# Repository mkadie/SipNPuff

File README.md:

# Sip and Puff Rubber Chicken Edition

## Project Overview

This project implements a functional sip and puff switch interface that serves as both a demonstration system (using rubber chickens) and a working, low-cost ($25-50) sip and puff device for accessibility applications. The core functionality focuses on creating a reliable, accessible interface while using the rubber chicken concept as an engaging demonstration tool for normally abled users.

---

## ⭐ Primary Claim to Fame: One Build, Many Purposes — Text File Configuration

> **The defining characteristic of this project is flexibility.**

Most open-source sip and puff devices are purpose-built for a single output: a USB mouse, a keyboard emulator, or a specific AT protocol. Changing what the device *does* means reflashing firmware or editing code. This project takes a different approach: **a single hardware build and a single firmware image that can be reconfigured for completely different tasks by editing a plain text configuration file** — no compiler, no IDE, no programmer required.

A clinician, caregiver, or technically capable user can open the config file (accessible as a USB drive when the device is plugged in) and change:
- What a sip or puff event maps to (keypress, mouse button, joystick axis, HID consumer control, serial command, etc.)
- Sensitivity thresholds for sip and puff, independently
- Operating mode (USB HID mouse, USB HID keyboard, XAC gamepad output, serial AT command relay, etc.)
- Head-tracking parameters (dead zone, speed curve, re-centre trigger gesture)
- Display content and feedback behaviour

The same physical device can serve as:
- A USB mouse (head tracking + sip/puff clicks)
- A two-switch keyboard input (sip = one key, puff = another)
- An Xbox Adaptive Controller input (via the onboard TRRS jacks)
- A demonstration interface (rubber chicken mode for Maker faires)
- A research data collection tool (with optional microSD logging)

No other project in the open-source sip and puff space offers this level of reconfigurability without touching firmware. This is intentional and is the core design goal that drives decisions about display hardware, the EXTERNAL_IO connector, STEMMA QT expansion, and the overall software architecture.

---

## Project Stage

Early, rapid development for prototype by Maker event, which one ... hopefully the next one :)

> **Firmware reference:** see [`FIRMWARE_NOTES.md`](./FIRMWARE_NOTES.md)
> for the current state of the CircuitPython firmware — pressure-sensor
> fusion, event-classifier rules, the on-screen HUD layout, the repeat-rate
> map, IMU pointing, and the full config-key reference. That's the document
> to read before touching `source/breath_classifier.py`,
> `source/sip_puff_device.py`, or any `config.txt` on a deployed device.

## Core Mission

### Primary Focus: Flexibility Through Text File Configuration
The defining goal is a single hardware and software build that can be reconfigured for a wide range of tasks by editing a plain text config file — no reflashing, no coding skills required. The same device adapts to the user, rather than requiring the user to adapt to a fixed device behavior.

### Secondary Focus: Functional Accessibility Interface
The main objective is to develop a robust, affordable sip and puff switch system that can be used for:
- Assistive technology for individuals with motor disabilities
- Accessibility solutions for communication devices
- Research in human-computer interaction
- Educational demonstrations in accessibility technology

### Tertiary Focus: Demonstration and Engagement
The rubber chicken concept serves as an engaging demonstration tool for:
- Maker faires and community events
- Educational outreach programs
- Public demonstrations of accessibility technology
- Engaging users in the concept of assistive interfaces

## Hardware Design

### Primary Components

#### Sensors

> **PCB Strategy:** Initial PCBs support both sensor footprints simultaneously. After real-world testing, separate PCB variants (SMD-only and through-hole) will be produced.

##### Default Sensor: LPS28DFWTR (SMD — I²C digital)
- **Part:** STMicroelectronics LPS28DFWTR
- **Package:** CCLGA-7L, 2.8 × 2.8 × 1.95 mm — SMD only, requires reflow or hot-air soldering
- **Why it's default:** Water-resistant package (potting gel, rated 10 ATM), 24-bit resolution, ultra-low noise (0.32 Pa), factory-calibrated, I²C interface, embedded FIFO, interrupt output, and 1.7 µA idle current
- **Interface:** I²C (up to 400 kHz fast mode; 1 MHz fast mode+) — connects directly to Pico W I²C bus
- **I²C address:** 0x5C (SA0 pin → GND) or 0x5D (SA0 pin → VDD) — selectable via PCB solder bridge
- **Pressure range:** Mode 1: 260–1260 hPa (optimised for sip/puff); Mode 2: 260–4060 hPa
- **Pressure noise:** 0.32 Pa RMS (Mode 1) — more than sufficient for breath detection
- **Accuracy:** ±0.5 hPa absolute, ±0.015 hPa relative
- **ODR:** 1–200 Hz (software configurable)
- **Supply voltage:** 1.7 to 3.6 V (3.3V from Pico W is within spec)
- **Interrupt:** INT_DRDY pin — data-ready interrupt for efficient polling
- **Datasheet:** DS13317 Rev 1, December 2021 (ST Microelectronics)
- **Sensor Placement:** Positioned in breath path between mouthpiece filter and PCB; water-resistant package tolerates condensation exposure

##### Alternative Sensor: MPX5010DP (Through-Hole — Analog output)
- **Part:** NXP/Freescale MPX5010DP
- **Package:** Through-hole SIP-6 — can be hand-soldered without SMD equipment
- **Why it's an alternative:** Easier to hand-solder for early prototypes and events; no SMD tools required
- **Interface:** **Analog voltage output** (0.2V–4.7V at 5V supply) — connects to a Pico ADC pin, **NOT I²C**
- **Pressure range:** 0–10 kPa differential
- **Supply voltage:** 2.7–5.5V (note: at 3.3V supply the output range scales; verify output headroom in firmware)
- **Accuracy:** ±1.5% FS
- **Power consumption:** ~6 mA typical (significantly higher than LPS28DFWTR)
- **Sensor Placement:** Same breath-path position; analog output wire routes to GPIO 26 (ADC0) on Pico W

#### Microcontroller
- **Raspberry Pi RP2040**: Chosen for its cost-effectiveness ($4), dual-core ARM Cortex-M0+ processor, and sufficient processing power for signal conditioning
- **Alternative Options**: 
  - ESP32 for WiFi connectivity
  - Arduino Nano for simpler implementations
  - STM32 for higher performance applications
- **Processing Requirements**: Signal filtering, input classification, and output protocol handling

#### Mechanical Interface
- **Primary Sip/Puff Mechanism**: 
  - Standard straw or tube for suction input
  - Blow tube for pressure input
  - Ergonomic design for comfortable use
- **Alternative Interfaces**: 
  - Custom 3D printed mouthpieces
  - Commercial sip/puff devices
  - Modular interface system for different user needs
- **Enclosure Design**: 
  - Durable, medical-grade materials
  - Easy-to-clean surfaces
  - Ergonomic housing for various user groups
- **Interface Options**: 
  - Standard straw configuration
  - Bellows system for precise suction detection
  - Custom mouthpiece designs

#### Optional Display Connectors

> Both connectors are unpopulated PCB footprints — built-in hardware support with no board redesign needed to add displays later.

##### J1 — I²C OLED Display (1", 128×64)
- **Connector**: 4-pin 2.54 mm Dupont header on PCB
- **Display type**: 1" 128×64 OLED, SSD1306 controller (or compatible)
- **Interface**: I²C — shares existing GPIO 4 (SDA) / GPIO 5 (SCL) bus with the LPS28DFWTR sensor
- **I²C address**: 0x3C (default) or 0x3D — no conflict with LPS28DFWTR at 0x5C/0x5D
- **Supply**: 3.3V
- **Pin order (1→4)**: GND → VCC → SCL → SDA
- **Use case**: Status readout, sip/puff feedback, pressure level bar graph

##### J2 — SPI Color LCD Display (2"–4")
- **Connector**: 9-pin 2.54 mm Dupont header on PCB
- **Display type**: 2"–4" color TFT LCD, ST7789 or ILI9341 controller (or compatible)
- **Interface**: SPI1 hardware peripheral on dedicated non-analog GPIO pins
- **GPIO assignments**:
  - GPIO 10 — SCK (SPI1 clock)
  - GPIO 11 — MOSI / SDI (SPI1 TX)
  - GPIO 12 — MISO / SDO (SPI1 RX, optional)
  - GPIO 13 — CS (chip select, active low)
  - GPIO 14 — DC/RS (high = data, low = command)
  - GPIO 15 — RESET (active low)
  - GPIO 16 — LED (backlight PWM; solder bridge for always-on 3.3V)
- **Pin order (1→9)**: VCC → GND → CS → RESET → DC/RS → MOSI → SCK → LED → MISO
- **Supply**: 3.3V
- **Use case**: Full-color rubber chicken game interface, animated demo display

#### Circuit Protection

> **A commonly overlooked step in open-source hardware projects, including many assistive technology designs.** External-facing I/O lines that connect to the real world — connectors, encoder inputs, expansion ports — are exposed to ESD events and electrical transients. Protecting the microcontroller's GPIO pins from these events is straightforward and inexpensive; skipping it is a common cause of latent damage in both hobby and clinical builds.

- **IC:** SP724AHTG — low-capacitance TVS (transient voltage suppressor) diode array, STMicroelectronics
- **Coverage:** All external-facing I/O lines **not** already protected by opto-isolation:
  - EXTERNAL_IO connector: BUTTON (GPIO 20), ROT_A (GPIO 18), ROT_B (GPIO 19), SDA (GPIO 4), SCL (GPIO 5)
  - STEMMA QT expansion port (SDA, SCL)
  - Display connectors J1 and J2 signal lines as applicable
- **Not needed on:** GPIO 0 (SIP_ENABLE) and GPIO 1 (PUF_ENABLE) — these are already isolated by PC817SC optocouplers before reaching the TRRS jacks
- **Why SP724AHTG:** Low capacitance preserves signal integrity on I²C and SPI lines; small package; single IC can protect multiple lines simultaneously; ~$0.30–0.50 per IC in single-unit quantities

#### Power Supply
- **Battery Option**: PCB designed to accommodate battery but not populated (user-selectable)
- **Optional LDO Power Supply**: For chair-based installations at events
- **Power Management**: 
  - Standalone operation with optional power expansion
  - Low power consumption design for battery operation
  - USB charging capability for convenience
- **Power Requirements**: 
  - Standby: <10mA
  - Active: <50mA
  - Battery life: >20 hours continuous operation

### Cost Analysis

| Component | Cost (single unit) | Notes |
|---|---|---|
| Pressure sensor — LPS28DFWTR | ~$4–6 | **Primary / default.** STMicroelectronics CCLGA-7L SMD; I²C, 24-bit, 0.32 Pa noise, water-resistant potting gel. Requires reflow or hot-air soldering. |
| Microcontroller | ~$4 | Raspberry Pi Pico W (RP2040 + CYW43439) |
| XAC output circuit | ~$2–3 | 2× PC817SC optocouplers + 2× TRRS jacks |
| Circuit protection | ~$1–2 | SP724AHTG TVS array ICs × 2–3 units; protects all I/O lines not covered by opto-isolators |
| Mechanical components | ~$5–10 | Tube, mouthpiece, connectors |
| Enclosure materials | ~$5–10 | 3D-printed or off-the-shelf housing |
| Miscellaneous | ~$5–10 | Resistors, caps, PCB, hardware |
| **Base build total** | **~$21–45** | Functional sip/puff device with XAC output and ESD protection |
| **Optional — MPX5010DP sensor** | **+~$3–5** | Through-hole analog alternative to the LPS28DFWTR; hand-solderable, no SMD tools required. *Depending on performance testing of the LPS28DFWTR vs MPX5010DP, this may remain a supported alternative or be retired from the design.* PCB includes footprint for both — only one is populated. |
| **Optional — BNO055 IMU** | **+~$30–35** | Bosch BNO055 on STEMMA QT breakout (e.g. Adafruit #4646); adds head-tracking (Mode A) and/or tongue-joystick cursor control (Mode B). Post-Maker-Faire upgrade — not required for core sip/puff functionality. Sensor alone costs more than the rest of the BOM combined at single-unit prices. |
| **Optional — display(s)** | **+~$5–15** | J1: 1" SSD1306 OLED ~$3–5; J2: 2–4" color LCD ~$8–15; PCB connectors already present |
| **Optional — hygiene filters** | **~$0.50–2 each** | Recurring consumable; see Section 10.1 of reference doc for filter options |
| **Full build with IMU + display** | **~$56–95** | Still well below comparable commercial AT devices ($175–$325+) |
| **Future / Medical-grade — redundant hardware** | **+~$15–30 est.** | For a medically certified build: a second LPS28DFWTR pressure sensor (cross-checks primary; flags discrepancy as fault condition) plus a second or dedicated safety CPU (hardware watchdog / supervisory MCU to monitor the primary RP2040 and force a safe state on failure). Required for IEC 62304 / FDA Class II pathway. Significant increase in PCB complexity and firmware scope. Not planned for current prototype — noted here as the architectural direction a certified variant would take. The lead designer has prior involvement in the design and manufacture of an FDA-regulated medical device (a lithium battery system for power wheelchairs, developed in conjunction with an established powerchair manufacturer), making this a realistic rather than purely aspirational future direction. See Section 10.7 of the reference doc for full detail. |

- **Manufacturing Considerations**: 
  - Scalable production design
  - Component sourcing for cost optimization
  - Quality control procedures

## Software Architecture

### Core Functionality

The system operates as a reliable, functional sip and puff interface with the following core features:

1. **Pressure Sensing**: Continuous monitoring of pressure sensor data with filtering — I²C polling (LPS28DFWTR default) or ADC sampling (MPX5010DP alternative)
2. **Input Classification**: Distinguishing between sip and puff actions with threshold detection
3. **Signal Processing**: Debouncing and smoothing of pressure readings
4. **Command Generation**: Converting pressure inputs into actionable commands
5. **Output Protocol**: Providing standardized outputs for various applications

### Input/Output Processing

#### Input Detection
- **Suction Detection**: Threshold detection for negative pressure (sip)
- **Blow Detection**: Threshold detection for positive pressure (puff)
- **Hold Detection**: Continuous pressure monitoring for extended commands
- **Debouncing**: Filtering for false triggers and noise reduction

#### Output Protocols
- **Digital Outputs**: 
  - Binary signals for on/off commands
  - Multi-level outputs for different command types
  - Serial communication for complex data transfer
- **Analog Outputs**: 
  - Voltage level representation of pressure
  - Proportional response for advanced applications
- **Communication Protocols**: 
  - I2C for LPS28DFWTR sensor communication (default); ADC for MPX5010DP (alternative)
  - UART for serial data transfer
  - USB for PC connectivity

### Command Structure
- **Basic Commands**: 
  - Sip (negative pressure)
  - Puff (positive pressure)
  - Hold (extended pressure)
- **Advanced Commands**: 
  - Double tap
  - Long press
  - Pattern recognition
- **Customizable Mapping**: 
  - User-defined command associations
  - Application-specific command sets

## Technical Specifications

### Electrical Specifications
- **Supply Voltage**: 3.3V or 5V (user selectable)
- **Current Consumption**: <50mA (standby), <100mA (active)
- **Operating Temperature**: -20°C to +70°C
- **Humidity Range**: 5% to 95% RH (non-condensing)
- **Input Impedance**: High impedance for sensor compatibility
- **Output Impedance**: Low impedance for reliable signal transmission

### Mechanical Specifications
- **Dimensions**: 150mm × 100mm × 50mm (approximate)
- **Weight**: <200g (excluding power source)
- **Input Force Range**: -500Pa to +500Pa
- **Response Time**: <100ms for pressure changes
- **Interface Materials**: Medical-grade, non-toxic materials
- **Durability**: >100,000 cycles of operation

### Performance Metrics
- **Accuracy**: ±2% for pressure measurements
- **Repeatability**: ±1% across multiple readings
- **Detection Threshold**: 50Pa for both suction and blowing
- **Operating Life**: >100,000 cycles
- **Reliability**: 99.5% uptime under normal conditions
- **Noise Resistance**: >60dB signal-to-noise ratio

## Accessibility Applications

### User Groups
- **Motor Disabled Individuals**: 
  - Spinal cord injury patients
  - Cerebral palsy users
  - ALS patients
  - Stroke recovery patients
- **Communication Needs**: 
  - Augmentative and alternative communication (AAC)
  - Voice output communication aids
  - Environmental control systems
- **Research Applications**: 
  - Motor function assessment
  - Rehabilitation technology
  - User interface studies

### Integration Capabilities
- **Communication Devices**: 
  - Text-to-speech systems
  - Voice synthesis units
  - Communication boards
- **Environmental Control**: 
  - Home automation systems
  - Lighting controls
  - Temperature regulation
- **Assistive Technology**: 
  - Wheelchair controls
  - Computer interface systems
  - Mobile device control

## Demonstration System (Rubber Chicken Concept)

### Purpose
- **Engagement Tool**: Make accessibility technology approachable and fun
- **Educational Aid**: Demonstrate principles of sip and puff technology
- **Community Outreach**: Attract attention to accessibility needs
- **Public Awareness**: Showcase assistive technology capabilities

### Demonstration Features
- **Rubber Chicken Interface**: 
  - Visual representation of the technology
  - Engaging user experience
  - Easy to understand concept
- **Interactive Gameplay**: 
  - Educational quiz system
  - Game-based learning
  - User engagement metrics
- **Public Display**: 
  - Maker faire setup
  - Educational booth
  - Community demonstration

### Technical Integration
- **Dual Functionality**: 
  - Real sip/puff system for actual use
  - Demonstration system for public engagement
- **Switching Mechanism**: 
  - User-selectable modes
  - Automatic mode detection
  - Context-aware operation

## Open Source Philosophy

### Documentation
- **Hardware**: Complete schematics, PCB layouts, BOM
- **Software**: Full source code with detailed comments
- **Assembly**: Step-by-step instructions
- **Calibration**: Testing and validation procedures
- **Applications**: Usage examples and integration guides

### Community Engagement
- **GitHub Repository**: Collaborative development environment
- **Issue Tracking**: Feature requests and bug reporting
- **Contribution Guidelines**: Clear development standards
- **Version Control**: Stable releases and development branches
- **Integration Tools**: Compatibility with maker ecosystem

## Research and Development Applications

### Academic Potential
- **Human-Computer Interaction**: 
  - Accessible interface design
  - User experience studies
  - Motor disability research
- **Assistive Technology**: 
  - Device development
  - User testing protocols
  - Technology evaluation
- **Engineering Education**: 
  - Hands-on learning projects
  - Design methodology
  - Prototyping techniques

### Publication Goals
- **IEEE Venues**: 
  - Accessibility technology papers
  - Human-computer interaction research
  - Assistive device development
- **Conference Presentations**: 
  - Maker faire demonstrations
  - Educational outreach
  - Research findings
- **Academic Papers**: 
  - Technical specifications
  - Performance analysis
  - User study results

## Scalability and Future Development

### Modular Design
- **Interface Expansion**: 
  - Different mechanical configurations
  - Customizable user interfaces
  - Modular component system
- **Protocol Support**: 
  - Multiple output standards
  - Integration with existing systems
  - Future-proof architecture
- **Upgrade Path**: 
  - Hardware improvements
  - Software enhancements
  - Feature additions

### Market Applications
- **Educational Institutions**: 
  - STEM learning tools
  - Engineering design projects
  - Accessibility education
- **Healthcare Providers**: 
  - Assistive technology solutions
  - Rehabilitation equipment
  - Clinical research tools
- **Research Labs**: 
  - Human-computer interaction studies
  - Device development
  - User interface research

## Conclusion

The Sip and Puff Rubber Chicken Edition represents a dual-purpose system that successfully balances accessibility functionality with community engagement. While the core focus remains on creating a reliable, affordable sip and puff interface for individuals with motor disabilities, the rubber chicken demonstration serves as an effective tool for public education and community outreach.

This approach ensures that the technology serves its primary purpose of supporting accessibility needs while also generating interest and understanding in the broader community. The system's modular design, open source nature, and focus on affordability position it well for both immediate practical applications and long-term research and development opportunities.

The project demonstrates how maker culture can contribute meaningfully to accessibility technology, creating solutions that are not only functional but also engaging and educational. By maintaining focus on the core sip and puff functionality while using the rubber chicken concept for demonstration, this system successfully bridges the gap between serious assistive technology and community engagement.

## Future

Taking inspiration from other sip and puff open source projects we will attempt to integrate mouse functionality after Maker Faire as time and schedule permit. The mouse feature is a software extension and should be comparatively easy.

### Head-Tracking via IMU (Phase 2 — Post-Maker-Faire)

The longer-term plan is to add **head-movement-based cursor control** using an IMU sensor, combining it with sip/puff for mouse clicks. This approach was validated in a peer-reviewed 2025 study ([S1] in the Reference doc) and is well-suited to users with high-level spinal cord injury or other conditions where oral motor control is limited.

**Selected sensor: Bosch BNO055** (~$30–35 on a STEMMA QT breakout)

The BNO055 was chosen over cheaper 6-DOF alternatives (MPU-6050, BMI270, LSM6DSOX) because it includes an on-board sensor fusion processor that outputs clean Euler angles and quaternions directly — no Kalman or Madgwick filter to implement. Its built-in magnetometer (9 DOF) also eliminates the yaw drift problem that affects 6-axis-only sensors during prolonged use, which is a real usability burden for a head mouse used over hours. The cost premium (~$25 over a basic IMU) is justified in context — it is a one-time addition, comparable in scale to a few rounds of replacement hygiene filters.

**Two mounting modes — same hardware, different placement:**

**Mode A — Head Strap / Glasses Mount:** The BNO055 is clipped to a glasses frame, forehead strap, or ear clip. Head nods and tilts move the cursor. Best for users with good head mobility. I²C wires run from the STEMMA QT port along the tube to the sensor on the head.

**Mode B — Tongue Joystick via Straw Attachment:** A small 3D-printed collar clips the BNO055 to the sip/puff tube near the mouthpiece. The user deflects the straw with their tongue — left, right, up, down — and the BNO055 detects the angular change of the tube. The straw becomes the joystick lever. Best for users with good tongue or lip control but limited head movement. Same hardware as Mode A, just repositioned.

With proper configuration the required activation force can be significantly reduced. The collar's position along the tube acts as a lever — moving it further from the tip lengthens the lever arm so a lighter tongue push produces a larger angular signal. Tube material flexibility also plays a role. On the software side, the sensitivity and dead zone settings in the config file can be tuned so that very small movements register as valid input without making the cursor jittery at rest. This makes Mode B viable for users with very limited tongue or lip strength, and gives clinicians a way to adjust force requirements without any hardware changes.

Switching between modes is a config file change (sensitivity, dead zone, and axis orientation parameters) — no reflashing required. This is a direct expression of the project's core flexibility goal.

**Hardware readiness:** No PCB changes are needed. The STEMMA QT expansion port (GPIO 4/5 I²C bus) is already present on the board for exactly this purpose. The BNO055's I²C address (0x28 or 0x29) does not conflict with any other device on the shared bus.

A three-way hybrid — head tracking, tongue joystick, and Hall-effect mouthpiece stick as selectable modes on the same hardware — is a longer-term stretch goal. No existing reviewed open-source project offers even two of these three options.

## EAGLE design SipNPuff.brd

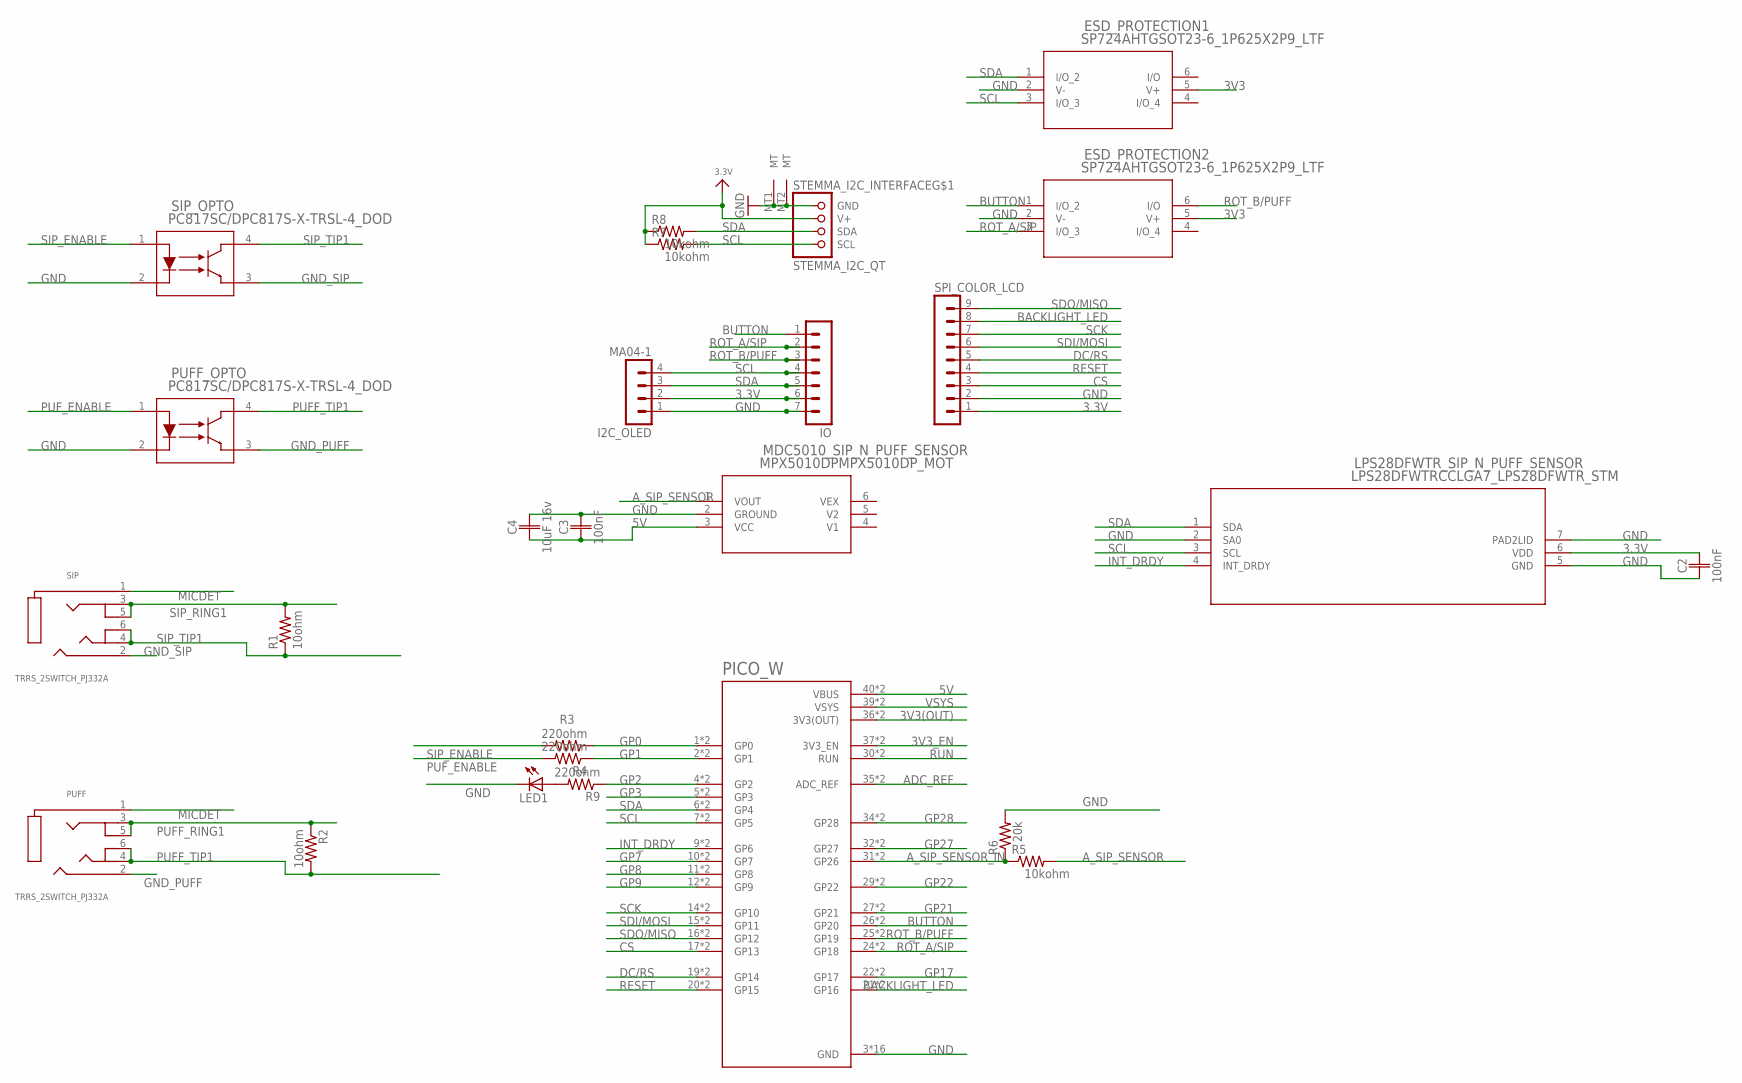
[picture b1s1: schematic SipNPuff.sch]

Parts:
C2, C3: 100nF; CAPC2012X110
C4: 10uF 16v; CAPC2012X110
ESD_PROTECTION1, ESD_PROTECTION2: SP724AHTGSOT23-6_1P625X2P9_LTF; SOT23-6_1P625X2P9_LTF
I2C_OLED: MA04-1
IO: MA07-1
LED1: LEDCHIP-LED0805; CHIP-LED0805
LPS28DFWTR_SIP_N_PUFF_SENSOR: LPS28DFWTRCCLGA7_LPS28DFWTR_STM; CCLGA7_LPS28DFWTR_STM
MDC5010_SIP_N_PUFF_SENSOR: MPX5010DPMPX5010DP_MOT; MPX5010DP_MOT
PICO_W: RASPBERRY_PICO-NO_DEBUG; PICO-PKG-NO_DEBUG
PUFF: TRRS_2SWITCH_PJ332A; PJ-332A
PUFF_OPTO: PC817SC/DPC817S-X-TRSL-4_DOD; SL-4_DOD
R1, R2: 10ohm; R0805
R3, R4, R9: 220ohm; R0805
R5, R7, R8: 10kohm; R0805
R6: 20k; R0805
SIP: TRRS_2SWITCH_PJ332A; PJ-332A
SIP_OPTO: PC817SC/DPC817S-X-TRSL-4_DOD; SL-4_DOD
SPI_COLOR_LCD: MA09-1
STEMMA_I2C_INTERFACE: STEMMA_I2C_QT; JST_SH4

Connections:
3.3V: C2.2, I2C_OLED.2 (B), IO.6, LPS28DFWTR_SIP_N_PUFF_SENSOR.6 (VDD), R7.1, R8.1, SPI_COLOR_LCD.1, STEMMA_I2C_INTERFACE.2 (V+)
3V3(OUT): PICO_W.36 (3V3(OUT)), PICO_W.P$36 (3V3(OUT))
3V3_EN: PICO_W.37 (3V3_EN), PICO_W.P$37 (3V3_EN)
5V: C3.1, C4.1, MDC5010_SIP_N_PUFF_SENSOR.3 (VCC), PICO_W.40 (VBUS), PICO_W.P$40 (VBUS)
ADC_REF: PICO_W.35 (ADC_REF), PICO_W.P$35 (ADC_REF)
A_SIP_SENSOR: MDC5010_SIP_N_PUFF_SENSOR.1 (VOUT), R5.2
A_SIP_SENSOR_IN: PICO_W.31 (GP26), PICO_W.P$31 (GP26), R5.1, R6.1
BACKLIGHT_LED: PICO_W.21 (GP16), PICO_W.P$21 (GP16), SPI_COLOR_LCD.8
BUTTON: ESD_PROTECTION2.1 (I/O_2), IO.1, PICO_W.26 (GP20), PICO_W.P$26 (GP20); also elsewhere on the board
CS: PICO_W.17 (GP13), PICO_W.P$17 (GP13), SPI_COLOR_LCD.3
DC/RS: PICO_W.19 (GP14), PICO_W.P$19 (GP14), SPI_COLOR_LCD.5
GND: C2.1, C3.2, C4.2, ESD_PROTECTION1.2 (V-), ESD_PROTECTION2.2 (V-), I2C_OLED.1 (A), IO.7, LED1.C, LPS28DFWTR_SIP_N_PUFF_SENSOR.2 (SA0), LPS28DFWTR_SIP_N_PUFF_SENSOR.5 (GND), LPS28DFWTR_SIP_N_PUFF_SENSOR.7 (PAD2LID), MDC5010_SIP_N_PUFF_SENSOR.2 (GROUND), PICO_W.3 (GND), PICO_W.8 (GND), PICO_W.13 (GND), PICO_W.18 (GND), PICO_W.23 (GND), PICO_W.28 (GND), PICO_W.33 (GND), PICO_W.38 (GND), PICO_W.P$3 (GND), PICO_W.P$8 (GND), PICO_W.P$13 (GND), PICO_W.P$18 (GND), PICO_W.P$23 (GND), PICO_W.P$28 (GND), PICO_W.P$33 (GND), PICO_W.P$38 (GND), PUFF_OPTO.2 (CATHODE), R6.2, SIP_OPTO.2 (CATHODE), SPI_COLOR_LCD.2, STEMMA_I2C_INTERFACE.1 (GND), STEMMA_I2C_INTERFACE.MT1 (MT), STEMMA_I2C_INTERFACE.MT2 (MT); also elsewhere on the board
GND_PUFF: PUFF.2 (RING1), PUFF_OPTO.3 (EMITTER)
GND_SIP: SIP.2 (RING1), SIP_OPTO.3 (EMITTER)
GP0: PICO_W.1 (GP0), PICO_W.P$1 (GP0), R3.1
GP1: PICO_W.2 (GP1), PICO_W.P$2 (GP1), R4.1
GP2: PICO_W.4 (GP2), PICO_W.P$4 (GP2), R9.1
GP3: PICO_W.5 (GP3), PICO_W.P$5 (GP3)
GP7: PICO_W.10 (GP7), PICO_W.P$10 (GP7)
GP8: PICO_W.11 (GP8), PICO_W.P$11 (GP8)
GP9: PICO_W.12 (GP9), PICO_W.P$12 (GP9)
GP17: PICO_W.22 (GP17), PICO_W.P$22 (GP17)
GP21: PICO_W.27 (GP21), PICO_W.P$27 (GP21)
GP22: PICO_W.29 (GP22), PICO_W.P$29 (GP22)
GP27: PICO_W.32 (GP27), PICO_W.P$32 (GP27)
GP28: PICO_W.34 (GP28), PICO_W.P$34 (GP28)
INT_DRDY: LPS28DFWTR_SIP_N_PUFF_SENSOR.4 (INT_DRDY), PICO_W.9 (GP6), PICO_W.P$9 (GP6)
MICDET: PUFF.1 (RING), SIP.1 (RING)
unnamed: LED1.A, R9.2
unnamed: ESD_PROTECTION1.5 (V+), ESD_PROTECTION2.5 (V+)
PUFF_RING1: PUFF.3 (RING2), PUFF.5 (R2_SW), R2.1
PUFF_TIP1: PUFF.4 (TIP), PUFF.6 (TIP_SW), PUFF_OPTO.4 (COLLECTOR), R2.2
PUF_ENABLE: PUFF_OPTO.1 (ANODE), R4.2
RESET: PICO_W.20 (GP15), PICO_W.P$20 (GP15), SPI_COLOR_LCD.4
ROT_A/SIP: ESD_PROTECTION2.3 (I/O_3), IO.2, PICO_W.24 (GP18), PICO_W.P$24 (GP18); also elsewhere on the board
ROT_B/PUFF: ESD_PROTECTION2.6 (I/O), IO.3, PICO_W.25 (GP19), PICO_W.P$25 (GP19); also elsewhere on the board
RUN: PICO_W.30 (RUN), PICO_W.P$30 (RUN)
SCK: PICO_W.14 (GP10), PICO_W.P$14 (GP10), SPI_COLOR_LCD.7
SCL: ESD_PROTECTION1.3 (I/O_3), I2C_OLED.4 (D), IO.4, LPS28DFWTR_SIP_N_PUFF_SENSOR.3 (SCL), PICO_W.7 (GP5), PICO_W.P$7 (GP5), R7.2, STEMMA_I2C_INTERFACE.4 (SCL); also elsewhere on the board
SDA: ESD_PROTECTION1.1 (I/O_2), I2C_OLED.3 (C), IO.5, LPS28DFWTR_SIP_N_PUFF_SENSOR.1 (SDA), PICO_W.6 (GP4), PICO_W.P$6 (GP4), R8.2, STEMMA_I2C_INTERFACE.3 (SDA); also elsewhere on the board
SDI/MOSI: PICO_W.15 (GP11), PICO_W.P$15 (GP11), SPI_COLOR_LCD.6
SDO/MISO: PICO_W.16 (GP12), PICO_W.P$16 (GP12), SPI_COLOR_LCD.9
SIP_ENABLE: R3.2, SIP_OPTO.1 (ANODE)
SIP_RING1: R1.2, SIP.3 (RING2), SIP.5 (R2_SW)
SIP_TIP1: R1.1, SIP.4 (TIP), SIP.6 (TIP_SW), SIP_OPTO.4 (COLLECTOR)
VSYS: PICO_W.39 (VSYS), PICO_W.P$39 (VSYS)

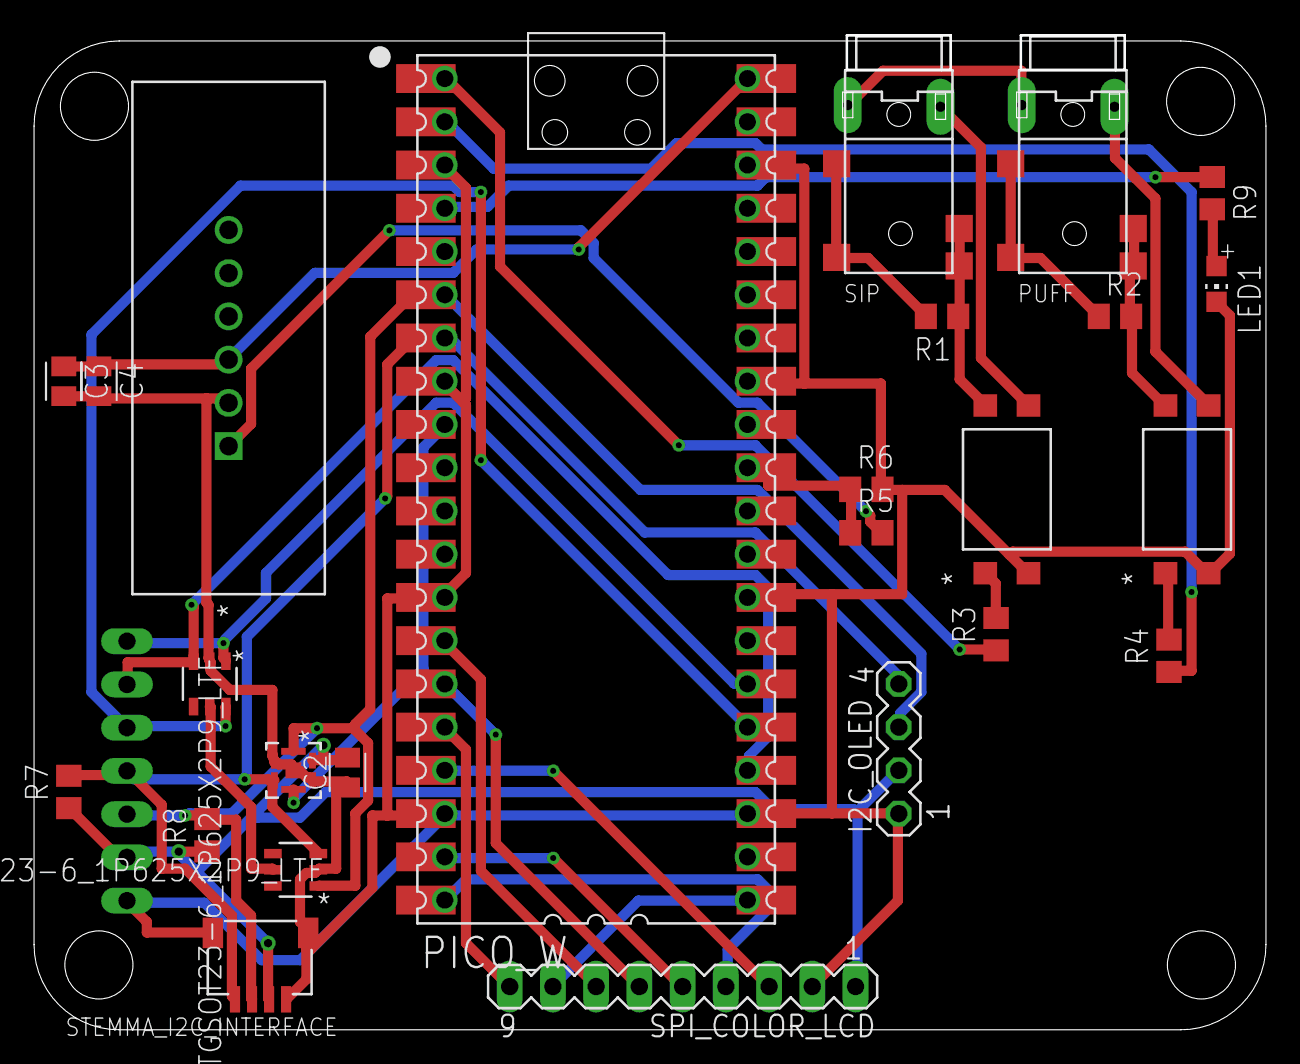
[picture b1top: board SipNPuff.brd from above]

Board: 2 copper layers, 72.4 x 58.1 mm, 26 parts (1 on the bottom side), 46 nets.

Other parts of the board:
U1, U2: SP724AHTGSOT23-6_1P625X2P9_LTF; SOT23-6_1P625X2P9_LTF

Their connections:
3V3: U1.5, U2.5
BUTTON: U1.1; also elsewhere on the board
GND: U1.2, U2.2; also elsewhere on the board
ROT_A/SIP: U1.3; also elsewhere on the board
ROT_B/PUFF: U1.6; also elsewhere on the board
SCL: U2.3; also elsewhere on the board
SDA: U2.1; also elsewhere on the board

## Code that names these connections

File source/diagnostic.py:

"""Benchtop diagnostic / calibration helper.

Streams pressure-sensor readings and classifier state to the serial
console without driving any outputs. Intended for:

  * Sanity-checking the voltage divider and decoupling
  * Picking sip/puff thresholds before flipping mode=run
  * Logging breath traces for a user-experience study

Switch to this mode by setting ``mode=diagnostic`` in /config.txt
on the CIRCUITPY drive — no code change required.

Output format (CSV-ish, one line per sample):

    diag t=12.345 raw=21345 v=1.073 sensor_v=1.610 abs=0.123 g=0.011 state=idle event=
"""

import time


def run(sensor, classifier, config, duration_s=None, display=None):
    """Stream readings until duration_s elapses (None → forever).

    Args:
        sensor: PressureSensor instance (already baseline-calibrated).
        classifier: BreathClassifier instance to display state from.
        config: runtime config dict.
        duration_s: optional cap, mostly used by automated tests.
        display: optional DisplayManager — if provided, visual
            bargraphs update in lockstep with the serial trace,
            so threshold picking can be done by eye.
    """
    poll_s = float(config.get("poll_period_s", 0.01))
    # Throttle the print to 50 Hz max — terminals don't like 200 Hz.
    print_interval = max(poll_s, 0.02)
    next_print = time.monotonic()
    t_start = time.monotonic()

    print("diag: streaming (poll={}s, print={}s)".format(poll_s, print_interval))
    print("diag: header t,raw,v,sensor_v,abs_kpa,gauge_kpa,state,event")

    event_counts = {"puff": 0, "double_puff": 0, "puff_repeat": 0,
                    "sip": 0, "sip_repeat": 0}

    try:
        while True:
            now = time.monotonic()
            if duration_s is not None and (now - t_start) >= duration_s:
                break

            raw = sensor.raw_average()
            v   = sensor.voltage(raw)
            sv  = sensor.sensor_v(raw)
            abs_p = sensor.pressure_kpa(raw)
            g_p   = abs_p - sensor.baseline_kpa
            event = classifier.poll(g_p)
            if event is not None:
                event_counts[event] = event_counts.get(event, 0) + 1

            if display is not None:
                display.update(g_p, classifier.state)

            if now >= next_print:
                next_print = now + print_interval
                print("diag t={:.3f} raw={} v={:.3f} sensor_v={:.3f} "
                      "abs={:.3f} g={:.3f} state={} event={}".format(
                          now - t_start, raw, v, sv, abs_p, g_p,
                          classifier.state, event or ""))

            time.sleep(poll_s)
    except KeyboardInterrupt:
        print("diag: interrupted")

    print("diag: event counts {}".format(event_counts))

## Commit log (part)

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2026-04-15 Initial commit of project
    Should be a rapid development for what I think will be a quick first working release
2026-04-15 Updates to include additional sensor
2026-04-15 Updated projected after researching and reviewing related / existing open source projects
2026-04-16 Additional updates from research and inspiration and move from .f3d to .sch and .brd format on electronics files for better sharing
2026-04-16 Updates based on additional research and inspiration. Moved from .f3d format for electronics to .sch and .brd from Eagle Cad as it is more standard
2026-04-16 Added PDF of schematice for more widespread review. It is quick and dirty, but everything is meaningfully labeled
2026-04-17 Added a use case where IMU is mounted directly to straw
2026-04-21 Updated documents based on iinspiration for FDA certification and parts cost
2026-05-02 Add readme.md for prototype photo documentation
    Added prototype photos of the T-Rex Sip-N-Puff HID electronics assembly
2026-05-02 Create README for 3D models and usage instructions
    Added a README file for 3D models including import instructions and notes.
2026-05-02 Incomplete 3d model
    Of first prototype not all electronic components have good models, but the Sensors are fully rendered and all the holes and connectors are in place for making plastic from
2026-05-02 Photos of 1st Article
    Photos from first article with both sip-n-puff sensor installed and showing 2 different optional displays OLED and Color LCD
2026-06-13 Add FUNDING.yml for project sponsorship options

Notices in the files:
parts and their libraries:
COPYRIGHT: Copyright (C) 2026 Ultra Librarian. All rights reserved.
COPYRIGHT: Copyright (C) 2022 Ultra Librarian. All rights reserved.
microbuilder: This work is placed in the public domain, and may be freely used for commercial and non-commercial work with the following conditions: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
